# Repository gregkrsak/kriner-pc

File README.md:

# Kriner Power Converter

A small open-source DC power switch with pushbutton controls and a separate logic-level enable input.

The Kriner Power Converter is designed to switch relatively high-current DC loads either from a microcontroller or from controls directly on the board. No firmware is required.

## What it does

The board uses a P-channel MOSFET as a high-side switch between `VIN` and `VOUT`.

There are three ways to control the output:

- **START** — manually enables `VOUT` while pressed.
- **STOP** — manually disables `VOUT` while pressed.
- **RUN** — logic-high input that enables `VOUT`.

`STOP` takes priority over either START or RUN.

In other words:

| START | STOP | RUN | VOUT |
| --- | --- | --- | --- |
| Released | Released | Low | Off |
| Pressed | Released | Low | On |
| Released | Released | High | On |
| Pressed | Released | High | On |
| Any | Pressed | Any | Off |

The pushbuttons are momentary controls rather than latching ON/OFF switches.

## Specifications

| | |
| --- | --- |
| Input voltage | 5–12 VDC |
| Switching | P-channel MOSFET, high side |
| Manual controls | START / STOP |
| External control | Logic-high RUN input |
| PCB size | Approximately 38.1 × 38.1 mm (1.5 × 1.5 in) |
| Construction | Through-hole |
| PCB layers | 2 |
| CAD format | EAGLE 6.5.0 |
| Design revision | 1.1 |
| Firmware | None |

The design has been tested from **5–12 VDC** and has been used with loads up to **15 A with forced-air cooling**.

See [Current and thermal notes](#current-and-thermal-notes) before treating 15 A as a continuous design rating.

## Connections

### Main header — JP1

| Pin | Signal | Purpose |
| --- | --- | --- |
| 1 | `VIN` | Positive supply input |
| 2 | `GND` | Ground |
| 3 | `GND` | Ground |
| 4 | `VOUT` | Switched positive output |
| 5 | `RUN` | Logic-high enable |

The board silkscreen identifies the same connections as:

`VIN` · `GND` · `GND` · `VOUT` · `RUN`

The RUN signal is named `5V` internally in the EAGLE schematic. It is intended as a logic-level control input for devices such as microcontrollers. A formal input-high threshold is not specified, so verify compatibility when using logic levels other than 5 V.

### 2 mm power connections

The board also provides separate 2 mm through-hole connections for:

- `VIN`
- `VOUT`
- `GND`
- `GND`

These provide an alternative to carrying load current through the main header.

## Circuit

The switching stage is built around an **FQP27P06 P-channel MOSFET** (`Q2`).

An **FJN3305RTA NPN transistor** (`Q1`) and three **1N4148** diodes combine the START and RUN inputs and control the MOSFET gate. The STOP switch acts directly on the gate-control network so that it overrides an asserted enable signal.

The basic logic is:

```text
                 +------ START button
                 |
Enable ----------+------ RUN logic input
                 |
                 v
          NPN control stage
                 |
                 v
VIN ------ P-channel MOSFET ------ VOUT
                 ^
                 |
                 +------ STOP button
```

This is a switch, not a voltage regulator: when enabled, `VOUT` is the switched version of `VIN`.

## Main components

| Ref. | Part | Description |
| --- | --- | --- |
| Q1 | FJN3305RTA | NPN transistor |
| Q2 | FQP27P06 | P-channel power MOSFET, TO-220 |
| D1–D3 | 1N4148 | Small-signal diodes |
| R1 | 10 kΩ | Resistor |
| R2 | 1 MΩ | Resistor |
| S1 | 6 mm tactile switch | START |
| S2 | 6 mm tactile switch | STOP |
| JP1 | 1×5 PTH header | Main connection header |

The PCB also includes two mounting/standoff holes and four dedicated 2 mm power connection holes.

## Schematic

The EAGLE schematic and board layout are included in the repository and can be modified directly.

## Repository layout

```text
kriner-pc/
├── eagle/
│   ├── kriner-pc.brd
│   └── kriner-pc.sch
├── images/
│   ├── kriner-pc-board.png
│   ├── kriner-pc-schmatic.png
│   └── oshw-logo-600-px-mirror.bmp
├── .gitignore
├── LICENSE
└── README.md
```

## Current and thermal notes

The Kriner Power Converter is an open-source hardware design rather than a fully characterized commercial power module.

The circuit has been tested from 5–12 VDC and has the potential to be used with loads up to 15 A with forced-air cooling. That figure should not be interpreted as a guaranteed continuous-current rating under arbitrary conditions.

Actual current capability depends on factors including:

- MOSFET dissipation and heatsinking
- PCB copper temperature
- airflow
- wiring and connector resistance
- ambient temperature
- load characteristics
- startup and inrush current

Additional characterization would be useful for:

- inrush current
- MOSFET power dissipation
- turn-on time
- turn-off time

For a new application, verify electrical and thermal behavior under the actual intended load.

## Project status

The EAGLE design files identify the current board as **Revision 1.1**.

Potential future work tracked in the repository includes:

- inrush-current characterization
- power-dissipation documentation
- turn-on and turn-off timing
- validation of a physical Rev. 1.2 board
- migration of the schematic to KiCad

The EAGLE `.sch` and `.brd` files are the canonical design files for the project.

## Open-source hardware

The Kriner Power Converter is open-source hardware. The schematic, PCB layout, and derived boards may be studied, modified, and shared under the terms of the project license.

The design and drawings are licensed under the **Creative Commons Attribution-ShareAlike 3.0 United States License (CC BY-SA 3.0 US)**.

See [LICENSE](LICENSE) for the complete license text.

---

Designed by **Greg M. Krsak**.

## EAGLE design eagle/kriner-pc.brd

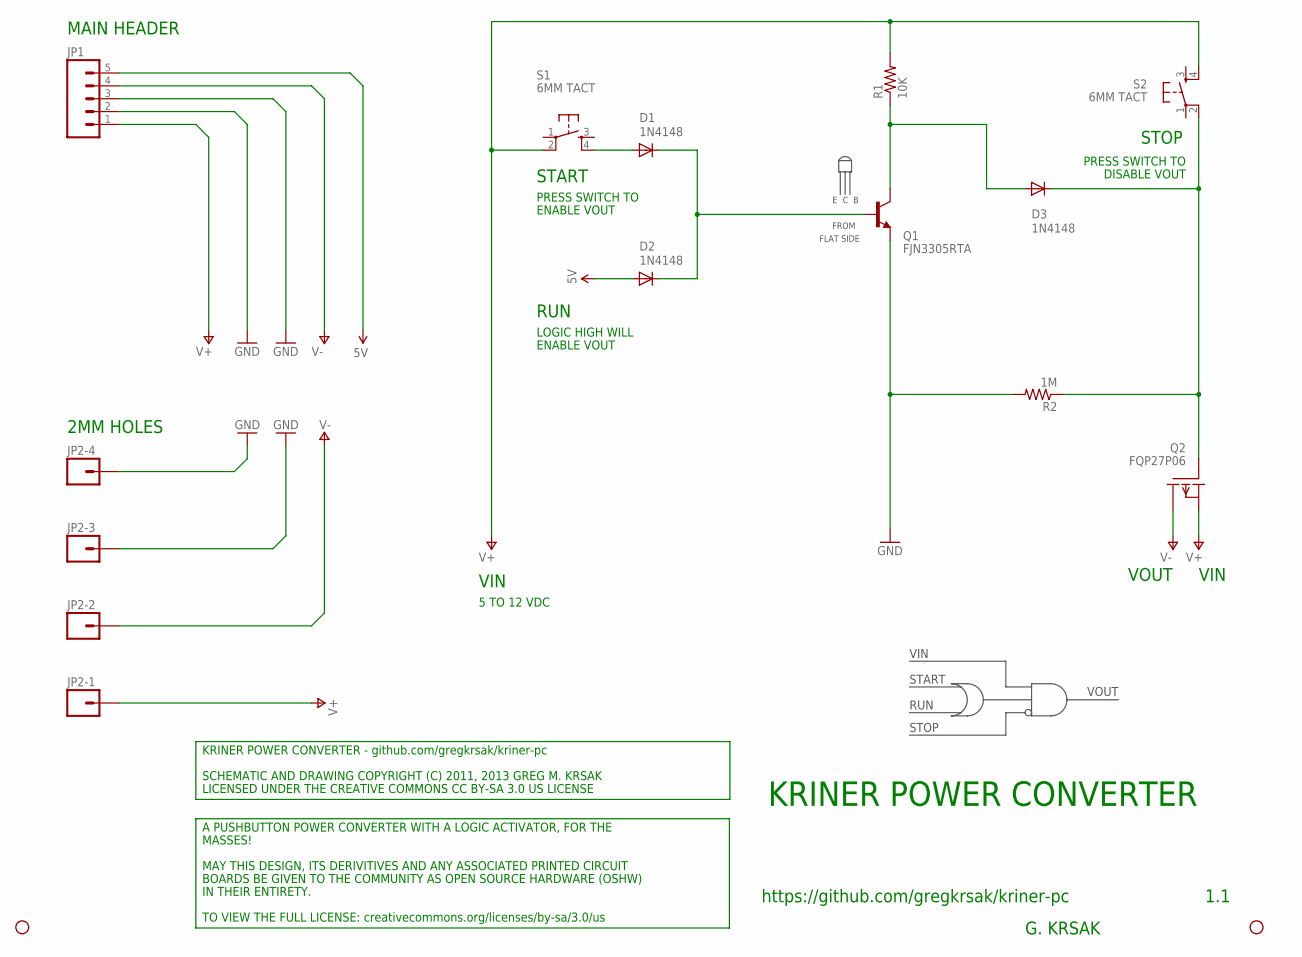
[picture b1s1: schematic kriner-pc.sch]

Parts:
D1, D2, D3: 1N4148; DIODE-1N4148
JP1: M05LOCK; 1X05_LOCK
JP2, JP3: STAND-OFF
JP2-1, JP2-2, JP2-3, JP2-4: M01PTH_2MM; 1X01_2MM
Q1: FJN3305RTA; TO92-ECB
Q2: FQP27P06; TO220
R1: 10K; AXIAL-0.3
R2: 1M; AXIAL-0.3
S1, S2: 6MM TACT; TACTILE-PTH

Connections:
5V: D2.A, JP1.5
GND: JP1.2, JP1.3, JP2-3.1, JP2-4.1, Q1.E, R2.P$2 (2)
unnamed: D1.C, D2.C, Q1.B
unnamed: D1.A, S1.4
unnamed: D3.C, Q2.1 (G), R2.P$1 (1), S2.2
unnamed: D3.A, Q1.C, R1.P$1 (1)
V+: JP1.1, JP2-1.1, Q2.3 (S), R1.P$2 (2), S1.2, S2.4
V-: JP1.4, JP2-2.1, Q2.2 (D)

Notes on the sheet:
1.1
https://github.com/gregkrsak/kriner-pc
KRINER POWER CONVERTER
START
STOP
RUN
VOUT
VIN
MAIN HEADER
2MM HOLES
A PUSHBUTTON POWER CONVERTER WITH A LOGIC ACTIVATOR, FOR THE
TO VIEW THE FULL LICENSE: creativecommons.org/licenses/by-sa/3.0/us
MAY THIS DESIGN, ITS DERIVITIVES AND ANY ASSOCIATED PRINTED CIRCUIT
BOARDS BE GIVEN TO THE COMMUNITY AS OPEN SOURCE HARDWARE (OSHW)
IN THEIR ENTIRETY.
KRINER POWER CONVERTER - github.com/gregkrsak/kriner-pc
LICENSED UNDER THE CREATIVE COMMONS CC BY-SA 3.0 US LICENSE
MASSES!
LOGIC HIGH WILL
ENABLE VOUT
PRESS SWITCH TO
DISABLE VOUT
5 TO 12 VDC
G. KRSAK
SCHEMATIC AND DRAWING COPYRIGHT (C) 2011, 2013 GREG M. KRSAK
FROM
FLAT SIDE

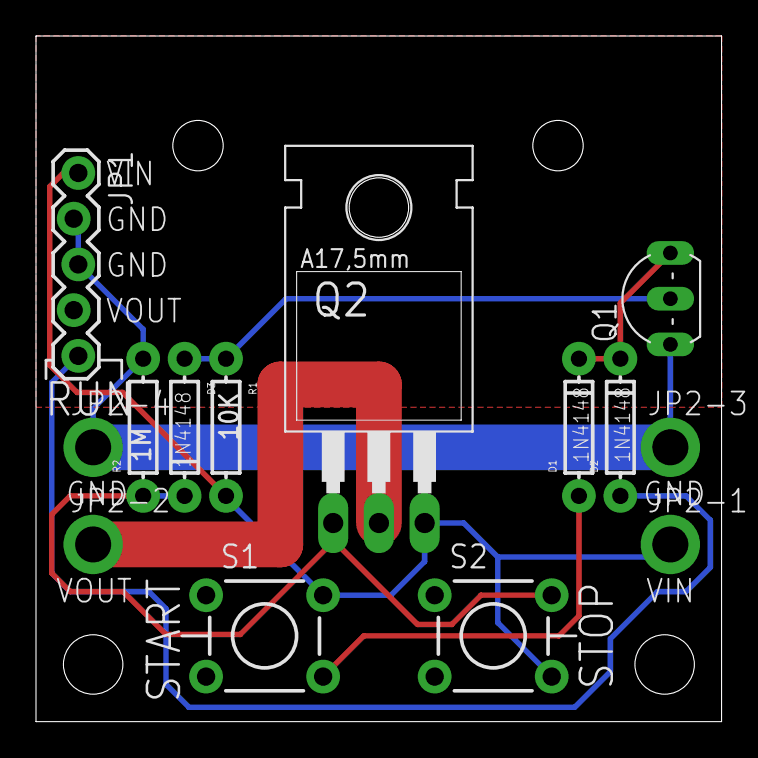
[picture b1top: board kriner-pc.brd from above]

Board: 2 copper layers, 38.1 x 38.1 mm, 16 parts (0 on the bottom side), 8 nets.

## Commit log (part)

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2013-10-09 Added .gitignore
2013-10-10 Closes #1.
2018-04-10 Expanded readme
2018-04-11 Added skills badge

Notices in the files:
eagle/kriner-pc.brd:
BOARD AND DRAWING COPYRIGHT (C) 2011, 2013 GREG M. KRSAK
eagle/kriner-pc.sch:
Users/gregkrsak/Desktop/GPL-v3-BMP.bmp
